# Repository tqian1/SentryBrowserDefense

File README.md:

# SentryBrowserDefense
ECE 492 Capstone Project

Folder organization:

## Extension
###### HeapExtension -> Contains our chrome extension heap snapshot tool.
###### ChromeSerialTest -> Contains our chrome extension serial interface.

## Embedded
###### SentryPeripheral -> Contains the code for our hardware peripheral.
###### ComponentTests -> Contains the code for testing our components.

## KiCad
###### sentry -> Contains the files surrounding design of our custom PCB.

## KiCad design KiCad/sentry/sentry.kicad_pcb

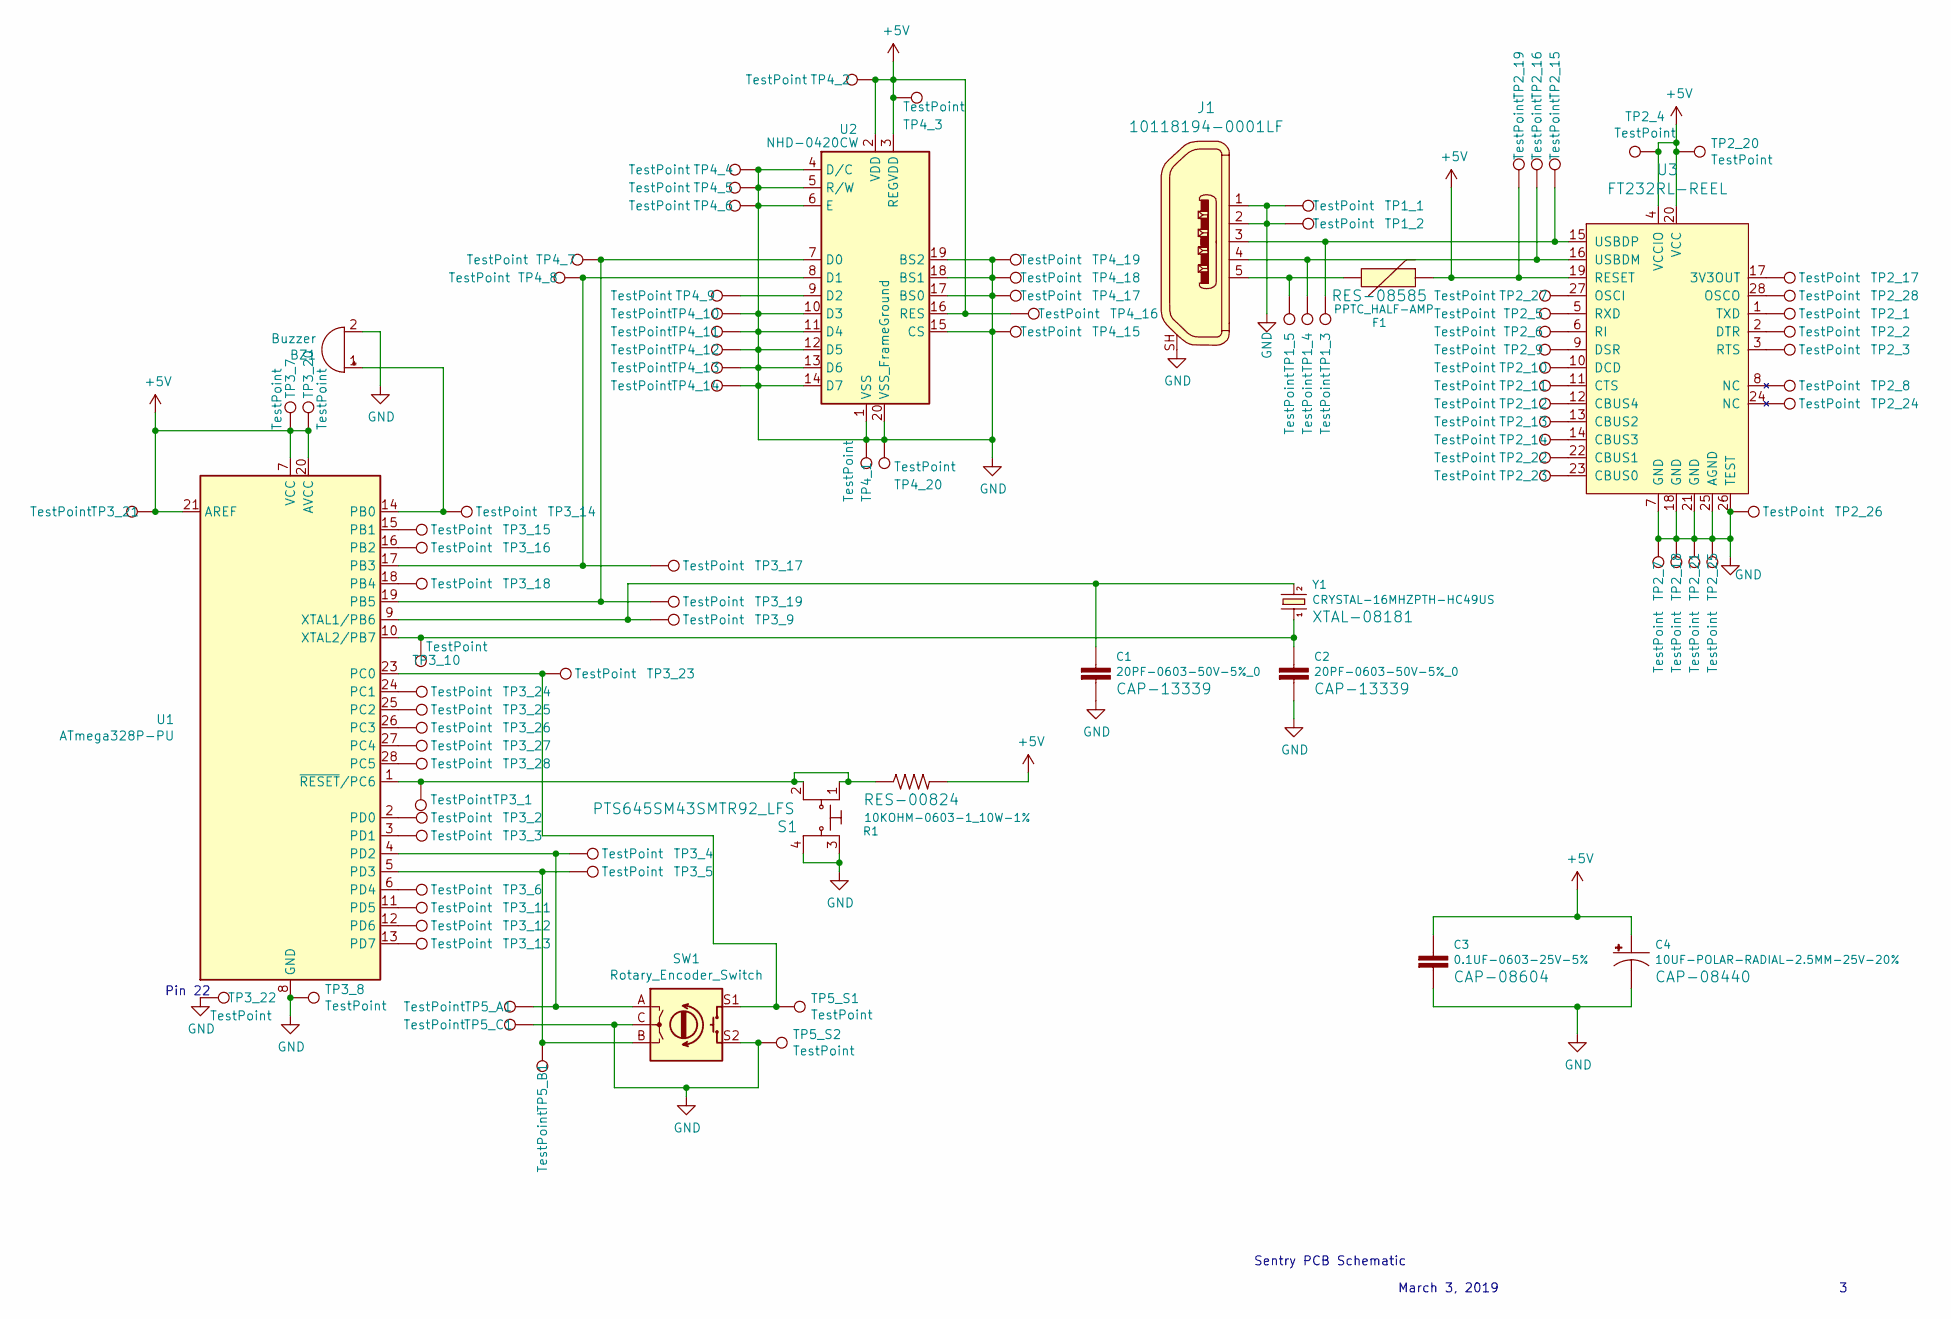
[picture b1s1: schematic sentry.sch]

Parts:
BZ1: Buzzer; BUZZER-12MM
C1, C2: 20PF-0603-50V-5%_0; 0603
C3: 0.1UF-0603-25V-5%; 0603
C4: 10UF-POLAR-RADIAL-2.5MM-25V-20%; CPOL-RADIAL-2.5MM-5MM
F1: PPTC_HALF-AMP; 1206
J1: 10118194-0001LF; USB_Micro_B_Female_10118194-0001LF; MPN 10118194-0001LF; Digi-Key_PN 609-4618-1-ND
R1: 10KOHM-0603-1_10W-1%; 0603
S1: PTS645SM43SMTR92_LFS; Switch_Tactile_SMD_6x6mm_PTS645; MPN PTS645SM43SMTR92 LFS; Digi-Key_PN CKN9112CT-ND
SW1: Rotary_Encoder_Switch; 90deg_rotary_encoder_switch
TP1_1, TP1_2, TP1_3, TP1_4, TP1_5, TP2_1, TP2_2, TP2_3, TP2_4, TP2_5, TP2_6, TP2_7, TP2_8, TP2_9, TP2_10, TP2_11, TP2_12, TP2_13, TP2_14, TP2_15, TP2_16, TP2_17, TP2_18, TP2_19, TP2_20, TP2_21, TP2_22, TP2_23, TP2_24, TP2_25, TP2_26, TP2_27, TP2_28, TP3_1, TP3_2, TP3_3, TP3_4, TP3_5, TP3_6, TP3_7, TP3_8, TP3_9, TP3_10, TP3_11, TP3_12, TP3_13, TP3_14, TP3_15, TP3_16, TP3_17, TP3_18, TP3_19, TP3_20, TP3_21, TP3_22, TP3_23, TP3_24, TP3_25, TP3_26, TP3_27, TP3_28, TP4_1, TP4_2, TP4_3, TP4_4, TP4_5, TP4_6, TP4_7, TP4_8, TP4_9, TP4_10, TP4_11, TP4_12, TP4_13, TP4_14, TP4_15, TP4_16, TP4_17, TP4_18, TP4_19, TP4_20, TP5_A1, TP5_B1, TP5_C1, TP5_S1, TP5_S2: TestPoint; TestPoint_THTPad_D1.5mm_Drill0.7mm
U1: ATmega328P-PU; DIP-28_W7.62mm
U2: NHD-0420CW; NHD_display
U3: FT232RL-REEL; SSOP-28_W5.30mm; MPN FT232RL-REEL; Digi-Key_PN 768-1007-1-ND
Y1: CRYSTAL-16MHZPTH-HC49US; HC49US

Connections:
+5V: C3.1, C4.1 (+), F1.2, R1.2, TP2_4.1, TP2_19.1, TP2_20.1, TP3_7.1, TP3_20.1, TP3_21.1, TP4_2.1, TP4_3.1, TP4_16.1, U1.7 (VCC), U1.20 (AVCC), U1.21 (AREF), U2.2 (VDD), U2.3 (REGVDD), U2.16 (RES), U3.4 (VCCIO), U3.19 (RESET), U3.20 (VCC)
GND: BZ1.2 (+), C1.2, C2.2, C3.2, C4.2 (-), J1.1, J1.2, J1.SH, S1.3, S1.4, SW1.C, SW1.S2, TP1_1.1, TP1_2.1, TP2_7.1, TP2_18.1, TP2_21.1, TP2_25.1, TP2_26.1, TP3_8.1, TP3_22.1, TP4_1.1, TP4_4.1, TP4_5.1, TP4_6.1, TP4_10.1, TP4_11.1, TP4_12.1, TP4_13.1, TP4_14.1, TP4_15.1, TP4_17.1, TP4_18.1, TP4_19.1, TP4_20.1, TP5_C1.1, TP5_S2.1, U1.8 (GND), U1.22 (GND), U2.1 (VSS), U2.4 (D/C), U2.5 (R/W), U2.6 (E), U2.10 (D3), U2.11 (D4), U2.12 (D5), U2.13 (D6), U2.14 (D7), U2.15 (CS), U2.17 (BS0), U2.18 (BS1), U2.19 (BS2), U2.20 (VSS_FrameGround), U3.7 (GND), U3.18 (GND), U3.21 (GND), U3.25 (AGND), U3.26 (TEST)
unnamed: BZ1.1 (-), TP3_14.1, U1.14 (PB0)
unnamed: C1.1, TP3_9.1, U1.9 (XTAL1/PB6), Y1.2
unnamed: C2.1, TP3_10.1, U1.10 (XTAL2/PB7), Y1.1
unnamed: F1.1, J1.5, TP1_5.1
unnamed: J1.3, TP1_3.1, TP2_15.1, U3.15 (USBDP)
unnamed: J1.4, TP1_4.1, TP2_16.1, U3.16 (USBDM)
unnamed: R1.1, S1.1, S1.2, TP3_1.1, U1.1 (~RESET~/PC6)
unnamed: SW1.A, TP3_4.1, TP5_A1.1, U1.4 (PD2)
unnamed: SW1.B, TP3_5.1, TP5_B1.1, U1.5 (PD3)
unnamed: SW1.S1, TP3_23.1, TP5_S1.1, U1.23 (PC0)
unnamed: TP2_1.1, U3.1 (TXD)
unnamed: TP2_2.1, U3.2 (DTR)
unnamed: TP2_3.1, U3.3 (RTS)
unnamed: TP2_5.1, U3.5 (RXD)
unnamed: TP2_6.1, U3.6 (RI)
unnamed: TP2_8.1, U3.8 (NC)
unnamed: TP2_9.1, U3.9 (DSR)
unnamed: TP2_10.1, U3.10 (DCD)
unnamed: TP2_11.1, U3.11 (CTS)
unnamed: TP2_12.1, U3.12 (CBUS4)
unnamed: TP2_13.1, U3.13 (CBUS2)
unnamed: TP2_14.1, U3.14 (CBUS3)
unnamed: TP2_17.1, U3.17 (3V3OUT)
unnamed: TP2_22.1, U3.22 (CBUS1)
unnamed: TP2_23.1, U3.23 (CBUS0)
unnamed: TP2_24.1, U3.24 (NC)
unnamed: TP2_27.1, U3.27 (OSCI)
unnamed: TP2_28.1, U3.28 (OSCO)
unnamed: TP3_2.1, U1.2 (PD0)
unnamed: TP3_3.1, U1.3 (PD1)
unnamed: TP3_6.1, U1.6 (PD4)
unnamed: TP3_11.1, U1.11 (PD5)
unnamed: TP3_12.1, U1.12 (PD6)
unnamed: TP3_13.1, U1.13 (PD7)
unnamed: TP3_15.1, U1.15 (PB1)
unnamed: TP3_16.1, U1.16 (PB2)
unnamed: TP3_17.1, TP4_8.1, U1.17 (PB3), U2.8 (D1)
unnamed: TP3_18.1, U1.18 (PB4)
unnamed: TP3_19.1, TP4_7.1, U1.19 (PB5), U2.7 (D0)
unnamed: TP3_24.1, U1.24 (PC1)
unnamed: TP3_25.1, U1.25 (PC2)
unnamed: TP3_26.1, U1.26 (PC3)
unnamed: TP3_27.1, U1.27 (PC4)
unnamed: TP3_28.1, U1.28 (PC5)
unnamed: TP4_9.1, U2.9 (D2)

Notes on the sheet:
Sentry PCB Schematic
March 3, 2019
Pin 22

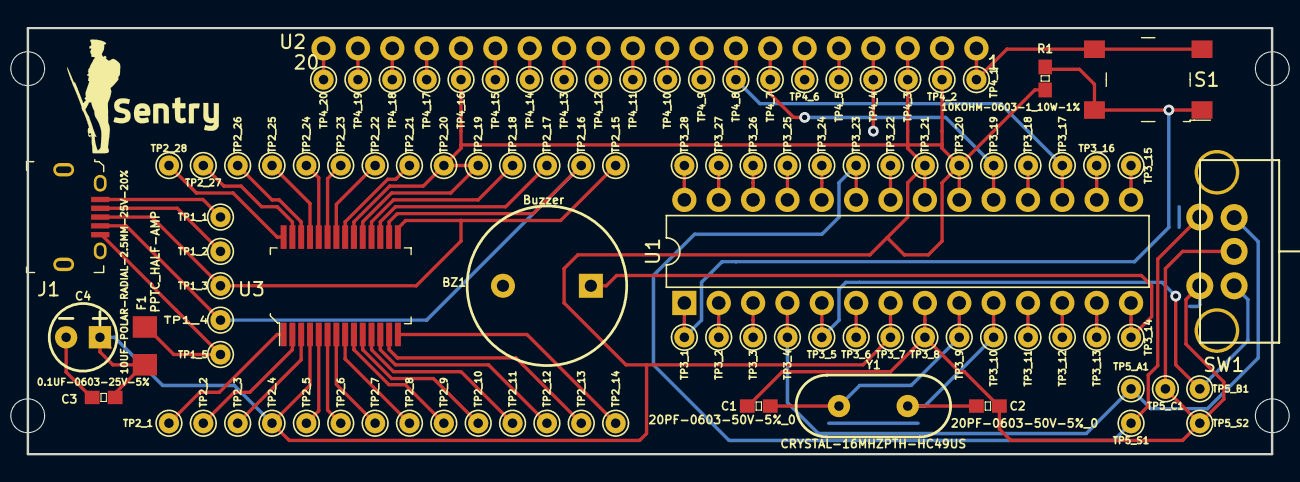
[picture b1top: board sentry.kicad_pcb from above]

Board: 2 copper layers, 91.9 x 31.5 mm, 100 parts (0 on the bottom side), 47 nets.

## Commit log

2019-02-04 add folders
2019-02-04 Created Chrome Arduino test
2019-02-04 small change to Arduino code
2019-02-04 removed unmodified 3rd party code
2019-02-04 add heap extension
2019-02-04 changed folder structure
2019-02-04 changes to heap snapshot tool
2019-02-04 change name
2019-02-04 added comment block to serial C test code
2019-02-04 Added comment blocks
2019-03-04 added IO test code
2019-03-04 added files
2019-04-05 add fullstack project
2019-04-05 boilerplate
2019-04-05 convert to blur admin templating
2019-04-05 readme
2019-04-05 git diff
2019-04-05 fixes
2019-04-05 refactor
2019-04-05 working
2019-04-05 more config
2019-04-05 main page changes
2019-04-05 more fixes:
2019-04-05 chrome extension fixes
2019-04-05 added dashboard
2019-04-05 got post and get requests working for features
2019-04-05 change dash
2019-04-08 Added code to test shortcodes for hardware actions.
2019-04-08 Revert "Added code to test shortcodes for hardware actions."
    This reverts commit 3d5c450a8a590cc352cd3c830886a8963059aa9b.
2019-04-08 upload stuff
2019-04-09 try diff upload
2019-04-09 scripts
2019-04-09 working file uploader
2019-04-09 uploads working
2019-04-09 fully working uploader
2019-04-09 remove snapshots
2019-04-09 gitignore fix
2019-04-09 git keep
2019-04-09 added browser
2019-04-09 auth
2019-04-10 more work
2019-04-10 charting
2019-04-10 added chart fixes
2019-04-10 added gitkeep
2019-04-10 rmeoved snapshots
2019-04-11 Add permissions for the site.
2019-04-11 Add https permissions for site.
2019-04-11 Remove comma.
2019-04-11 Add some basic get code to test API
2019-04-12 added files
    I still need to properly document them
2019-04-12 documented code
